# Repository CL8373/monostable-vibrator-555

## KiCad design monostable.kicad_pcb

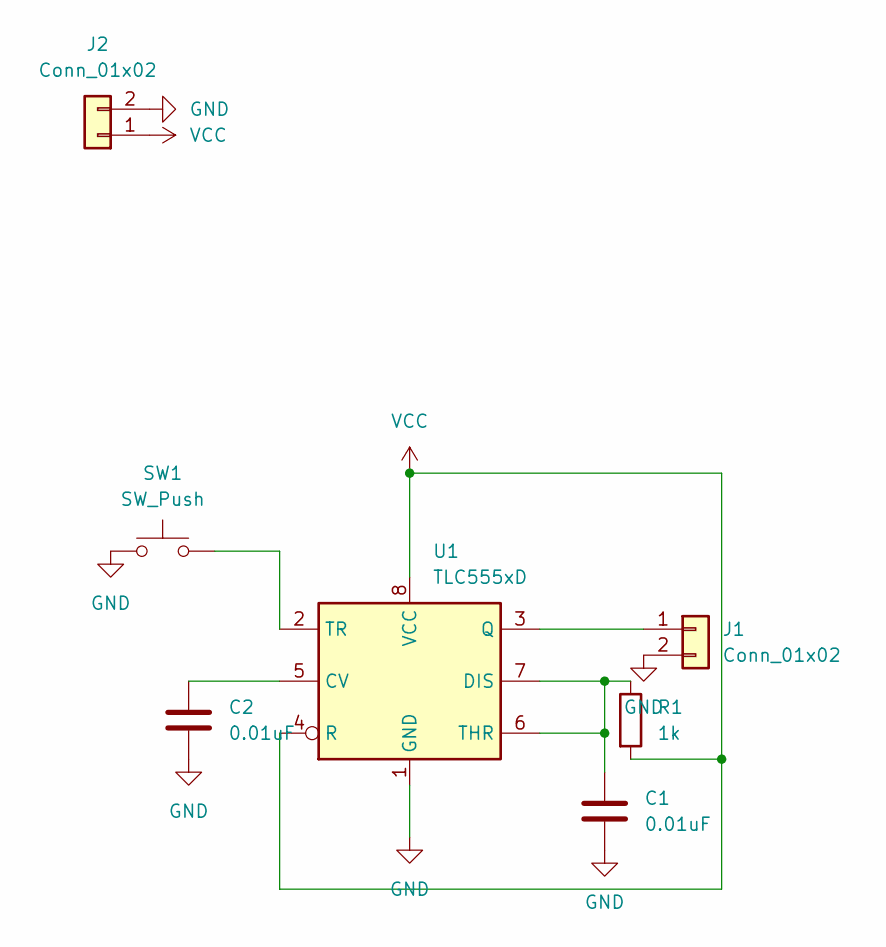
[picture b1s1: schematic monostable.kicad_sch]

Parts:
C1, C2: 0.01uF; C_1206_3216Metric_Pad1.33x1.80mm_HandSolder
J1, J2: Conn_01x02; output connector
R1: 1k; R_1206_3216Metric_Pad1.30x1.75mm_HandSolder
SW1: SW_Push; SW4_PTS815 SJM 250 SMTR LFS_CNK
U1: TLC555xD; SOIC-8_3.9x4.9mm_P1.27mm

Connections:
GND: C1.2, C2.2, J1.2, J2.2, SW1.1, U1.1 (GND)
unnamed: J1.1, U1.3 (Q)
unnamed: C2.1, U1.5 (CV)
unnamed: C1.1, R1.1, U1.6 (THR), U1.7 (DIS)
unnamed: SW1.2, U1.2 (TR)
VCC: J2.1, R1.2, U1.4 (R), U1.8 (VCC)

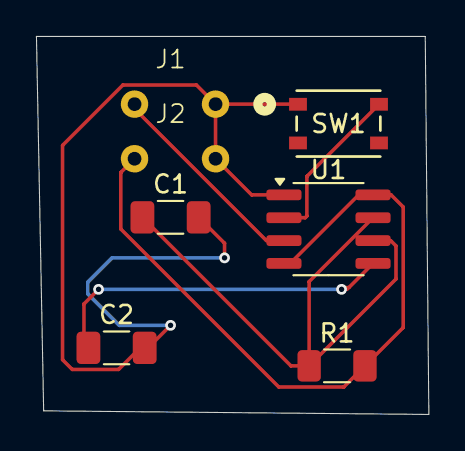
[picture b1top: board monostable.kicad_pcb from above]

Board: 2 copper layers, 21.8 x 21.0 mm, 7 parts (0 on the bottom side), 6 nets.

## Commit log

2024-10-28 monostable vibrator 555
